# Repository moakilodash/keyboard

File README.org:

#+title: keyboard

my keyboard project collection.

adding here diy keyboard builds:

+ [[file:boards/moaki_/README.org][moaki_]] - modified ferris sweep, wired (qmk with helios 0xCB)

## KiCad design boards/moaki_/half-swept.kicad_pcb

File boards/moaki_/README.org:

#+title: moaki_

my first attempt at building a keyboard.

~moaki_~ is a modified version of [[https://github.com/davidphilipbarr/sweep][half-swept]] revertible board.

wired (using helios 0xCB microcontroller), 34-key column-stagger split

will later update here with more infomration about this build, including pictures...

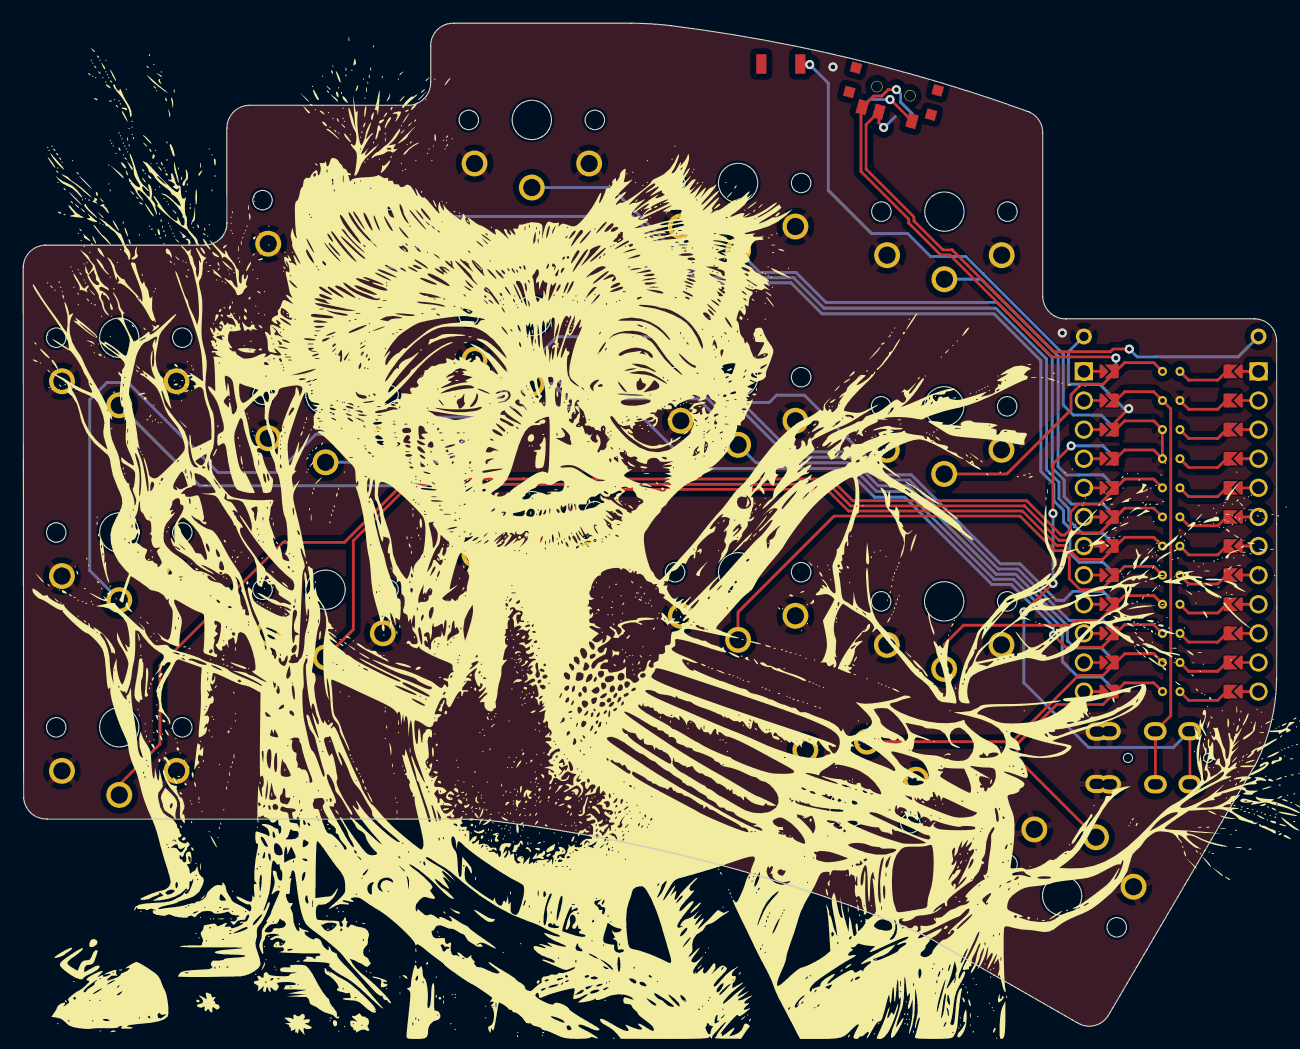
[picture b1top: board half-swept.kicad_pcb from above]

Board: 2 copper layers, 109.4 x 87.5 mm, 23 parts (0 on the bottom side), 22 nets.

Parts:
B+: MountingHole_Pad; 1pin_conn
B-: MountingHole_Pad; 1pin_conn
J2: AudioJack4dpb; TRRS-PJ-DPB2
POWER SW: SW_SPDT; SPDT_C128955
RSW2: SW_Push; Tactile-Switch_SMT
SW1, SW2, SW3, SW4, SW5, SW6, SW7, SW8, SW9, SW10, SW11, SW12, SW13, SW14, SW15, SW16, SW17: SW_Push; SW_PG1350_rev_DPB
U1: ProMicro-kbd; ProMicro_jumpers_facedown

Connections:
BT+_r: B+.1, POWER SW.2
Switch1: SW1.1, U1.10
Switch2: SW2.1, U1.17
Switch3: SW3.1, U1.18
Switch4: SW4.1, U1.19
Switch5: SW5.1, U1.20
Switch6: SW6.1, U1.16
Switch7: SW7.1, U1.15
Switch8: SW8.1, U1.14
Switch9: SW9.1, U1.13
Switch10: SW10.1, U1.1
Switch11: SW11.1, U1.5
Switch12: SW12.1, U1.6
Switch13: SW13.1, U1.7
Switch14: SW14.1, U1.8
Switch15: SW15.1, U1.9
Switch16: SW16.1, U1.11
Switch17: SW17.1, U1.12
Switch18: J2.R1, U1.2
gnd: B-.1, J2.S, J2.T, SW1.2, SW2.2, SW3.2, SW4.2, SW5.2, SW6.2, SW7.2, SW8.2, SW9.2, SW10.2, SW11.2, SW12.2, SW13.2, SW14.2, SW15.2, SW16.2, SW17.2, U1.3, U1.4, U1.23
raw: POWER SW.3, U1.24
vcc: J2.R2, U1.21

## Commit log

2026-02-15 init: my version of ferris sweep build
2026-02-21 chore: update directory structure and the half-swept edge cut
2026-02-23 chore: update traces, add footprint for silkscreen and mask, modify the edge cut
2026-02-25 final -- add cool silkscreen, reduce errors and wardnings from kicad
2026-03-27 update: consolidate .gitignore to repo root, covering kicad temp files and zmk west workspace; add moaki_ qmk firmware files and photos placeholder
2026-03-27 add: readme
